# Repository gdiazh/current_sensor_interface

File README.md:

Content
---------------------
---------------------

# Current Sensor Interface

-[Arduino Controller.](#controller)

-[Comunication Interface.](#interface)

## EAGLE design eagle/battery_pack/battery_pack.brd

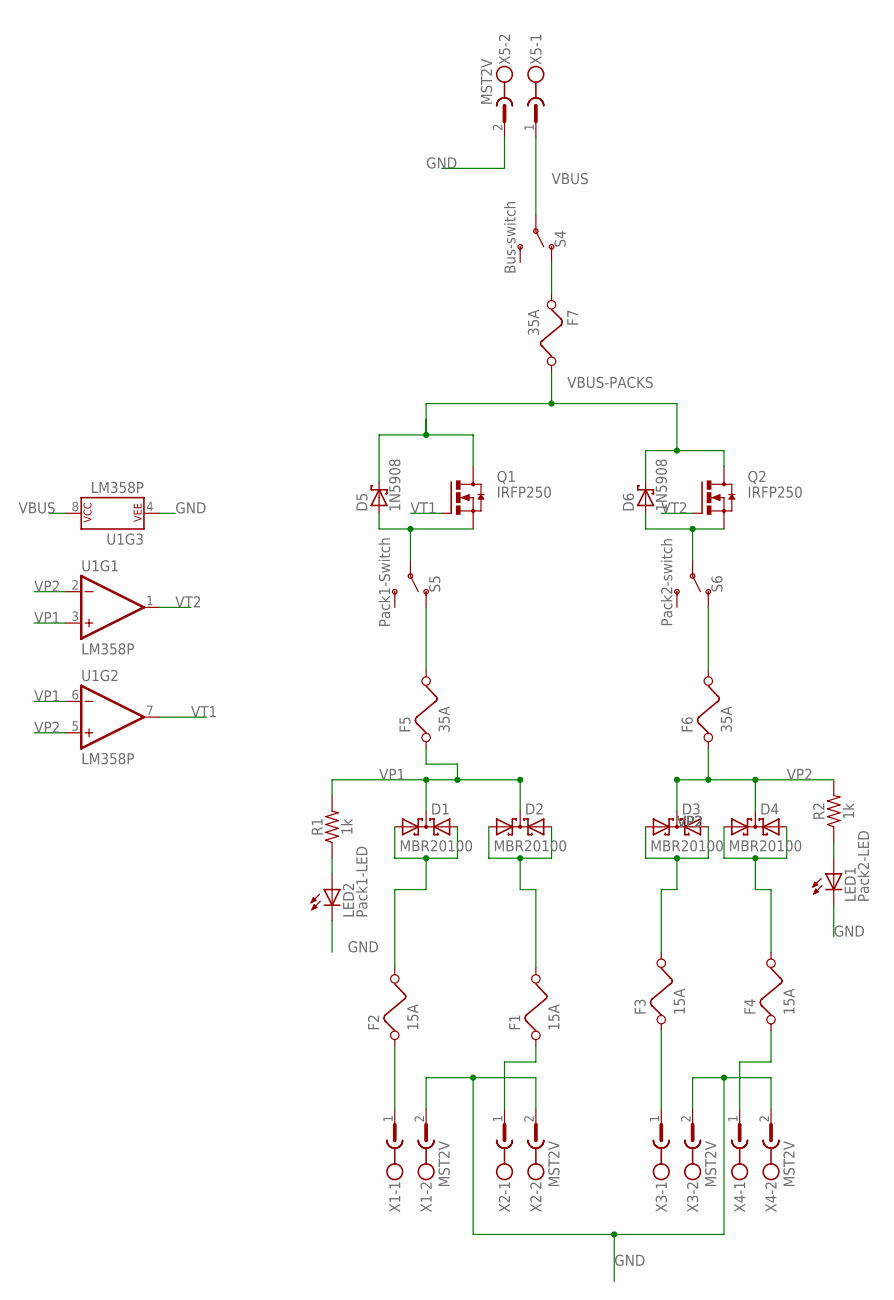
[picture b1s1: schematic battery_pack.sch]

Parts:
D1, D2, D3, D4: MBR20100; SOT82L
D5, D6: 1N5908; C4111-15
F1, F2, F3, F4: 15A; FUSE
F5, F6, F7: 35A; FUSE
LED1: Pack2-LED; Q62902-B156
LED2: Pack1-LED; Q62902-B156
Q1, Q2: IRFP250; TO-247AD-V
R1, R2: 1k; AXIAL-0.4
S4: Bus-switch; SWITCH_SPDT_PTH_11.6X4.0MM_LOCK
S5: Pack1-Switch; SWITCH_SPDT_PTH_11.6X4.0MM_LOCK
S6: Pack2-switch; SWITCH_SPDT_PTH_11.6X4.0MM_LOCK
U1: LM358P; DIP08_LONGPAD
X1, X2, X3, X4, X5: MST2V; MSTBV2

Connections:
GND: LED1.K (C), LED2.K (C), U1.4 (P$V-), X1.2, X2.2, X3.2, X4.2, X5.2
unnamed: F2.1, X1.1
unnamed: F3.1, X3.1
unnamed: F1.1, X2.1
unnamed: D1.A1, D1.A2, F2.2
unnamed: D2.A1, D2.A2, F1.2
unnamed: D3.A1, D3.A2, F3.2
unnamed: D4.A1, D4.A2, F4.2
unnamed: D5.A, Q1.S, S5.2
unnamed: D6.A, Q2.S, S6.2
unnamed: LED2.A, R1.P$1 (1)
unnamed: LED1.A, R2.P$1 (1)
unnamed: F6.2, S6.1 (O)
unnamed: F7.1, S4.1 (O)
unnamed: F5.2, S5.1 (O)
unnamed: F4.1, X4.1
VBUS: S4.2, U1.8 (P$V+), X5.1
VBUS-PACKS: D5.C, D6.C, F7.2, Q1.D, Q2.D
VP1: D1.C, D2.C, F5.1, R1.P$2 (2), U1.3 (+IN), U1.6 (-IN)
VP2: D3.C, D4.C, F6.1, R2.P$2 (2), U1.2 (-IN), U1.5 (+IN)
VT1: Q1.G, U1.7 (OUT)
VT2: Q2.G, U1.1 (OUT)

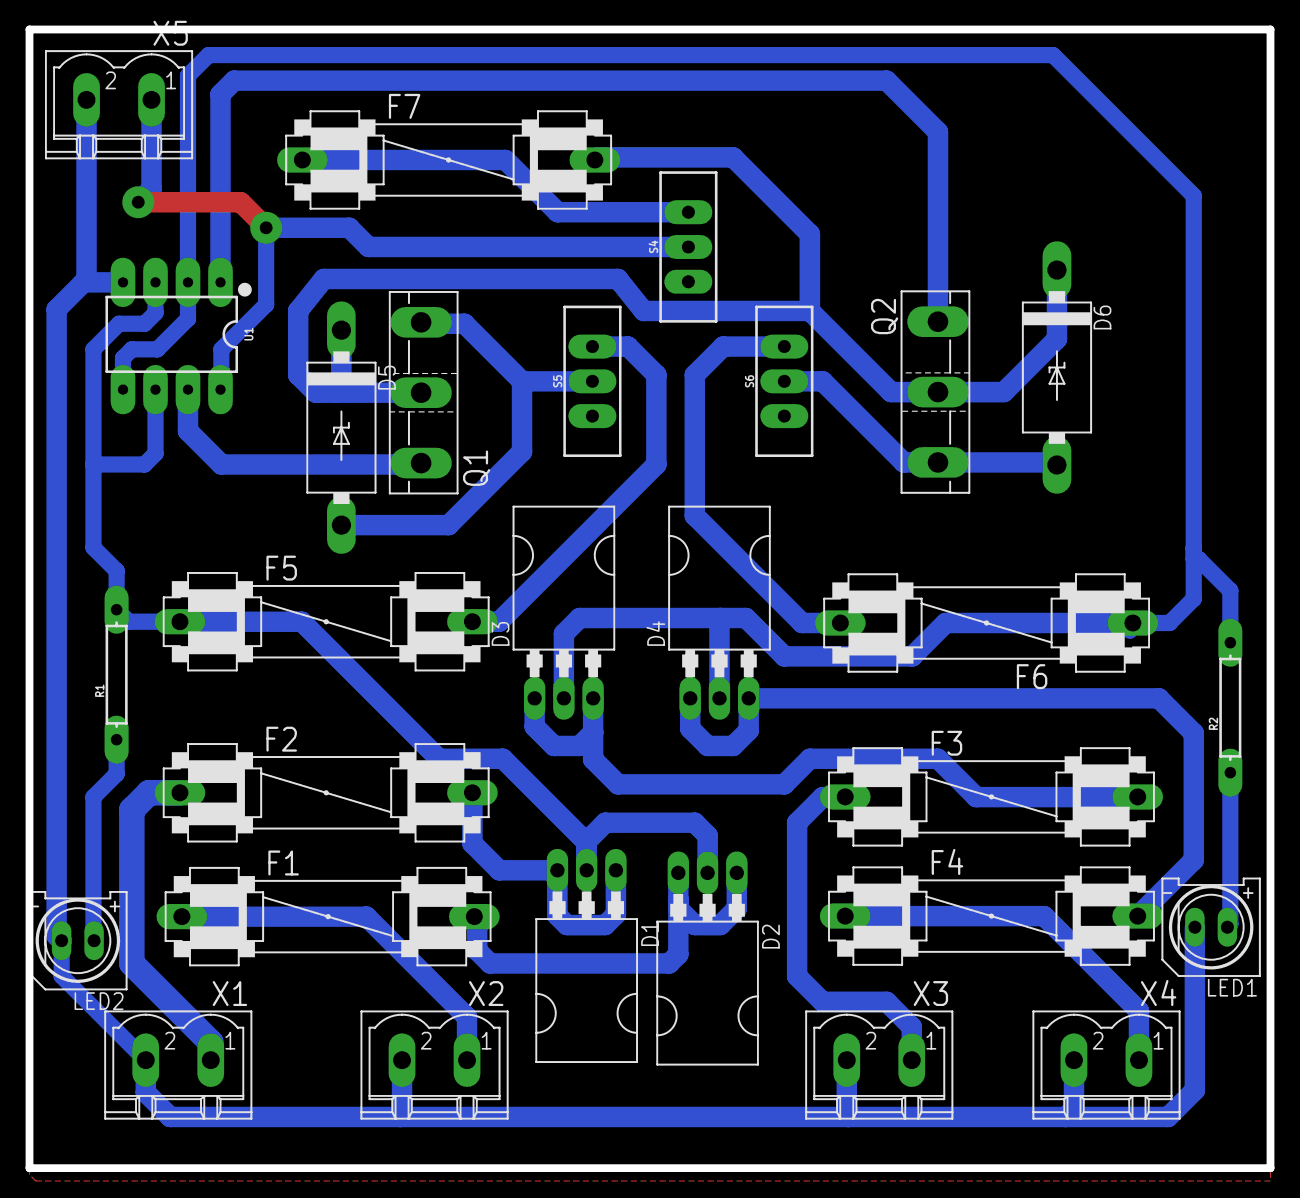
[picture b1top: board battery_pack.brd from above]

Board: 2 copper layers, 97.0 x 89.0 mm, 28 parts (0 on the bottom side), 22 nets.

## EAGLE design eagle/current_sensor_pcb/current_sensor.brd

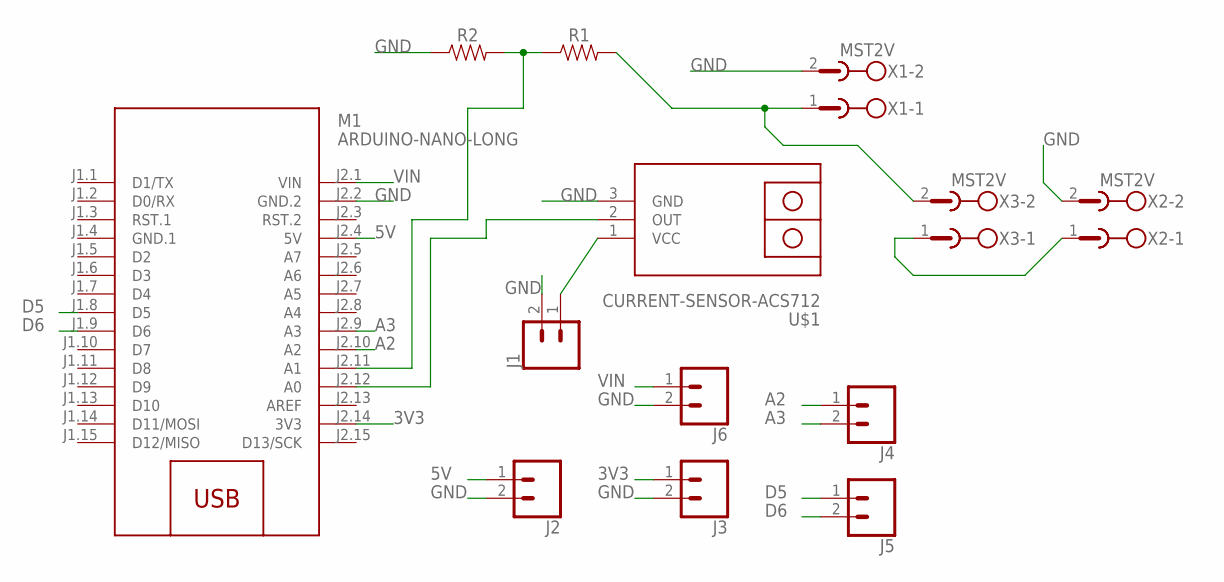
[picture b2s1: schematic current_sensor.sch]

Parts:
J1, J2, J3, J4, J5, J6: CONN_02LOCK_LONGPADS; 1X02_LOCK_LONGPADS
M1: ARDUINO-NANO-LONG
R1, R2: AXIAL-0.3
U$1: CURRENT-SENSOR-ACS712
X1, X2, X3: MST2V; MSTBV2

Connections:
3V3: J3.1, M1.J2.14 (3V3)
5V: J2.1, M1.J2.4 (5V)
A2: J4.1, M1.J2.10 (A2)
A3: J4.2, M1.J2.9 (A3)
D5: J5.1, M1.J1.8 (D5)
D6: J5.2, M1.J1.9 (D6)
GND: J1.2, J2.2, J3.2, J6.2, M1.J2.2 (GND.2), R2.P$1 (1), U$1.3 (GND), X1.2, X2.2
GND.1: M1.J1.4 (GND.1)
unnamed: M1.J2.12 (A0), U$1.2 (OUT)
unnamed: R1.P$2 (2), X1.1, X3.2
unnamed: J1.1, U$1.1 (VCC)
unnamed: M1.J2.11 (A1), R1.P$1 (1), R2.P$2 (2)
unnamed: X2.1, X3.1
VIN: J6.1, M1.J2.1 (VIN)

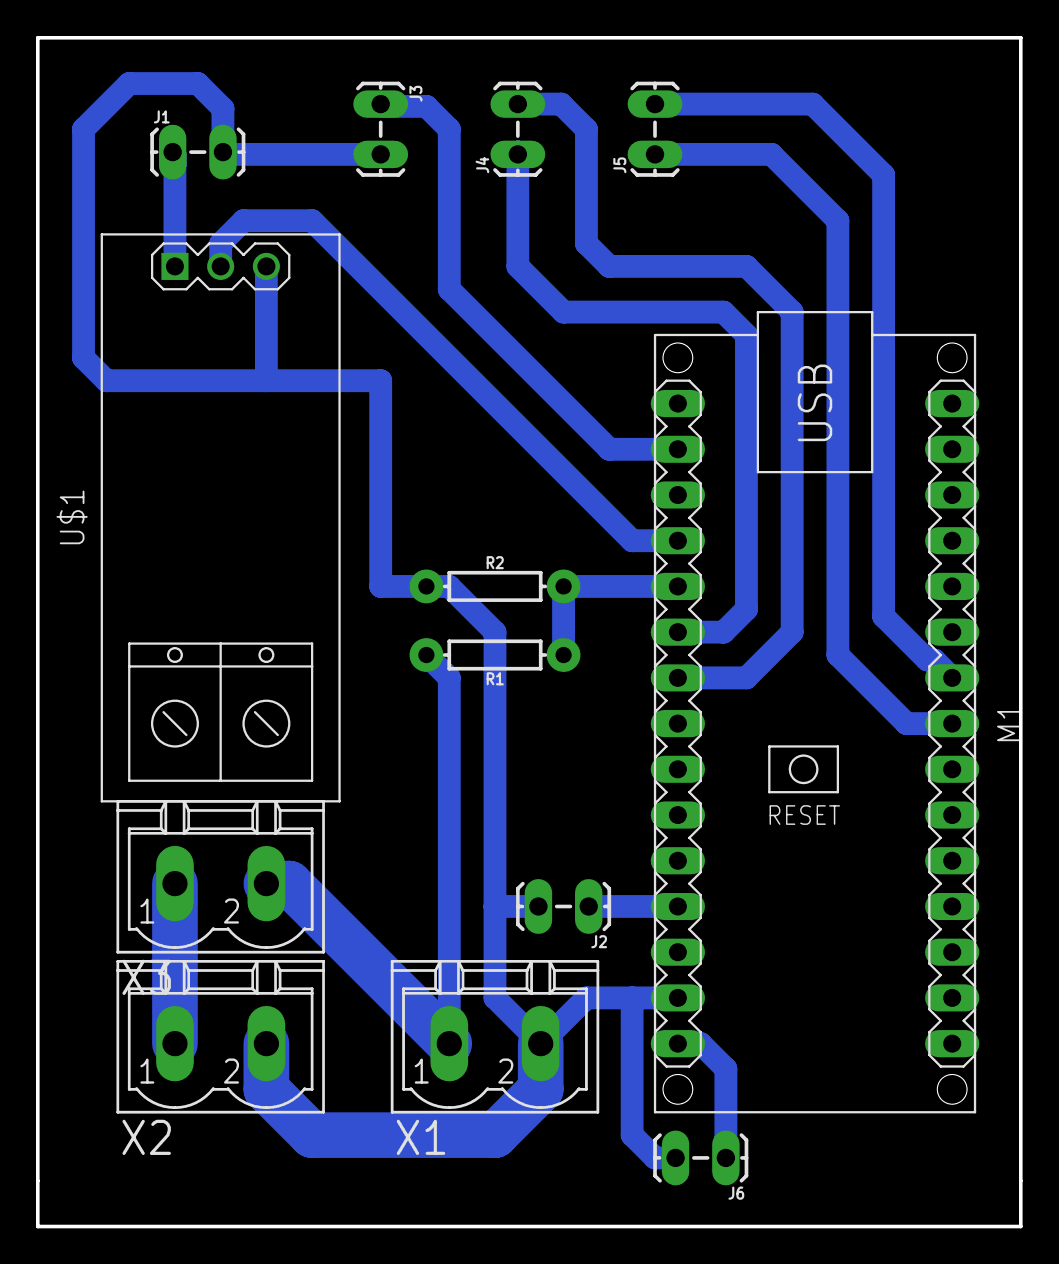
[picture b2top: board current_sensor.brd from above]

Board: 2 copper layers, 54.6 x 66.0 mm, 13 parts (0 on the bottom side), 13 nets.

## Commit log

2017-10-06 arduino driver and ros interface
2017-10-06 added sensor unit convertion
2017-10-06 fix calibration
2017-10-14 pcb eagle files
2017-10-20 pcb design ready
2017-10-25 voltage measure calibrated
2017-11-03 agregue la integral(sum) y el coef
2017-11-07 modified mesurement units
2017-11-15 battery monitor for sensor
2017-11-19 battery pack pcb

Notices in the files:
parts and their libraries:
SparkFun-IC-Amplifiers: Licensing: Creative Commons ShareAlike 4.0 International - https://creativecommons.org/licenses/by-sa/4.0
diy-modules: Released under the Creative Commons Attribution 4.0 International License: http://creativecommons.org/licenses/by/4.0
